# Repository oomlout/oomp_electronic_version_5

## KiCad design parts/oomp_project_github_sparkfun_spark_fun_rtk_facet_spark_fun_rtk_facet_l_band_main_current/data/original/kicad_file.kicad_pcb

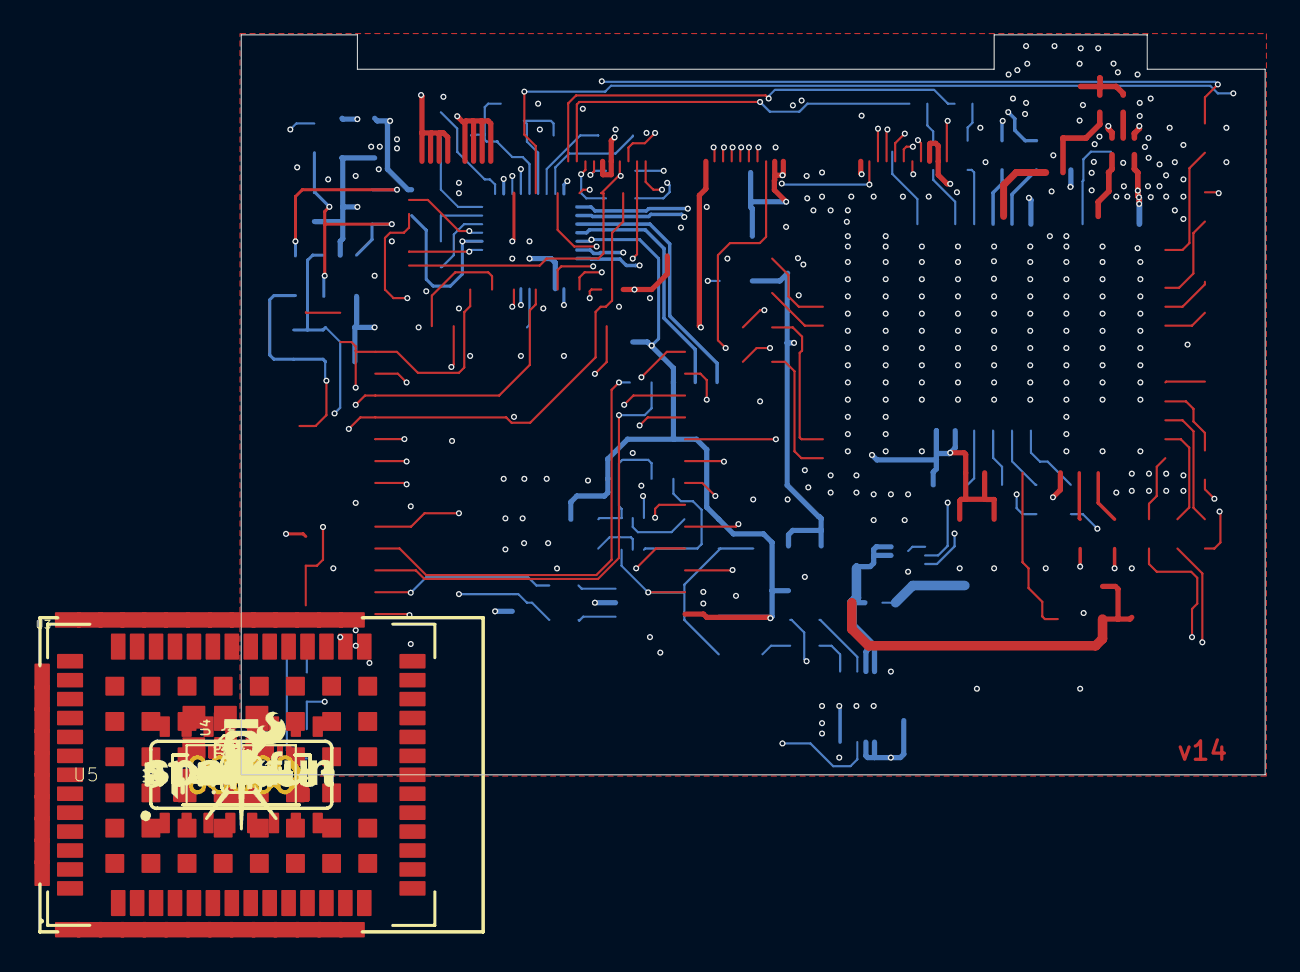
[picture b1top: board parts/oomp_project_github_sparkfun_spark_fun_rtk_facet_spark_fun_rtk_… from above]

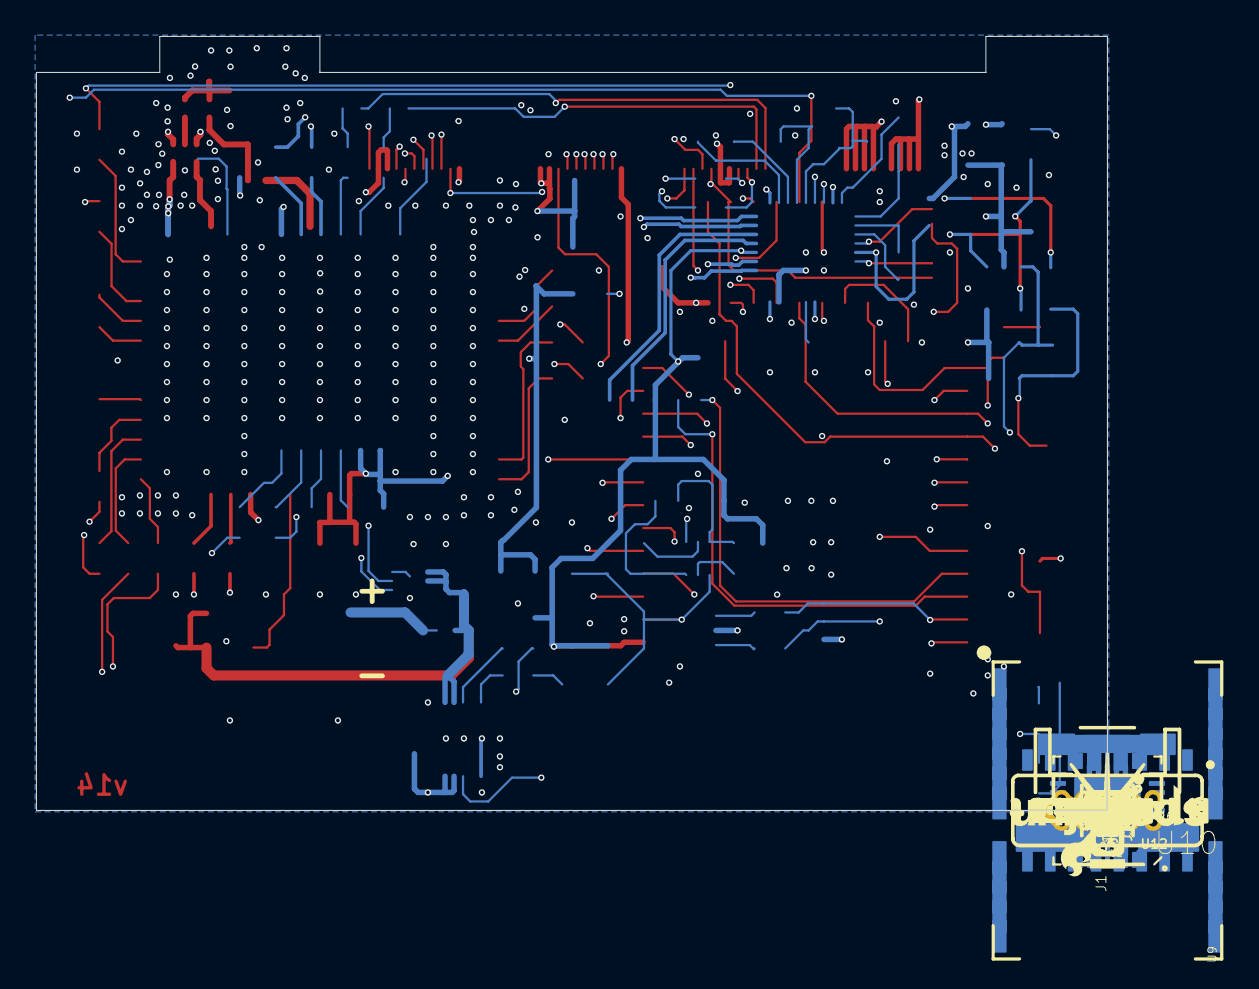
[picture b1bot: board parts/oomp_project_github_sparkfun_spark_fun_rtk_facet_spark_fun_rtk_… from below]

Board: 4 copper layers, 59.5 x 43.0 mm, 153 parts (89 on the bottom side), 109 nets.

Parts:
C2, C4, C6, C17, C18, C25, C27, C30, C31: 1.0uF; 0603
C3, C16: 4.7uF; 0603
C5, C7, C8, C11, C12, C13, C15, C21, C22, C23, C24, C26, C28, C29: 0.1uF; 0603
C9, C19: 18pF; 0603
C10, C14, C20: 10uF; 0603
C32, C33: 47pF; 0402-TIGHT
D1: Yellow; LED-0603
D2, D7: 3A/10V/280mV; SOD-323
D4: 250mA/100V; SOD-323
D5: PESD0402; 0402-TIGHT
FB2: 2.66Ω; 0402-TIGHT
FRAME1, FRAME2: FRAME-LEDGER; CREATIVE_COMMONS
J1: QWIIC_RIGHT_ANGLE; JST04_1MM_RA
J2: U.FL
J3: 1X01_NO_SILK
J4, J14: 1X02_NO_SILK
J7: JST-2-SMD
J8, J10, J15, J18: FPC_12_DOUBLESIDED_BACKFLIP
J9: CORTEX_JTAG_DEBUG_PTH; 2X5-PTH-1.27MM
JP1, JP2: SMT-JUMPER_2_NO_SILK
JP3, JP4: SMT-JUMPER_2_NC_TRACE_SILK
JP7: JUMPER-SMT_3_NO_SILK; SMT-JUMPER_3_NO_SILK
JP21, JP61, JP71, JP81: FIDUCIALUFIDUCIAL; FIDUCIAL-MICRO
LOGO1: OSHW-LOGOMINI; OSHW-LOGO-MINI
LOGO2, LOGO3: SFE_LOGO_NAME_FLAME.1_INCH; SFE_LOGO_NAME_FLAME_.1
MEAS2: JUMPER-COMBO_2_NC_TRACE; COMBO-JUMPER_2_NC_TRACE
Q2: MBT3904DW1T1; SC70-6
Q3: SIL2308; SOT26
R1, R2, R3, R4, R9, R14, R15, R35, R36, R37, R38, R41, R42, R45, R46, R47, R48, R49, R50: 33; 0603
R5: 12k; 0603
R6, R11, R33: 1k; 0603
R7, R12: 2.2k; 0603
R8: 0; 0603
R10, R20, R22, R23, R29, R31: 10k; 0603
R13: 1M; 0603
R16, R17, R18, R19, R21, R26: 100k; 0603
R24: 300k; 0603
R25, R32: 22; 0603
R27, R28, R39, R40: 27; 0603
R30: 150k; 0603
R34: 4.7k; 0603
R43: 100; 0603
R44: 10; 0402-TIGHT
TP1, TP2: TEST-POINT3X5; PAD.03X.05
U1: 74HC4052D; SO16
U2, U12: AP2112K-3.3V; SOT23-5
U3: U-BLOX_ZED-F9P; ZED-F9P
U4: STLQ015-3.3V; SOT23-5
U5: ESP-WROOM-3232D-DFMP; ESP-WROOM-32D-DFM_PASTE
U6: CH340C; SO016
U7: MAX17048; DFN-8
U8: USB251XB; QFN-36
U9: U-BLOX_NEO-D9S-00B; NEO-M9N_M8T_M8U_D9S_F9P
U10: MCP73833MSOP; MSOP10
U13: POWER-DIVIDER; PD0922J5050S2HF_ANA
U$1: LIPO0
U$2: SPECIAL_INSTRUCTIONS-ORDERING; ORDERING_INSTRUCTIONS
U$3: EC21
U$4: SD#DIS0
U$5, U$7: L#BAND0
U$6: #3V3#0
U$8: EC10
U$10: #PPS#1
U$11, U$13: RTK_FACET0
U$12: RADIO0
U$14, U$84: #GND#1
U$15, U$16: RTK5#SVG0
U$17: ANTENNA1
U$18: L1#L2#L0
U$24: STAT0
U$25: #I�C#0
U$26: ##ERST##0
U$30: QWIIC_4MM
Y1: 24MHz; CRYSTAL-SMD-2.0X1.6MM

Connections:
3.3V: C2.1, C7.2, C8.1, C25.1, C26.2, C30.1, C31.1, J1.2, J4.1, J8.3, J8.4, J10.3, J10.4, J18.5, J18.6, JP7.2, U1.16, U3.33, U3.34, U3.38, U9.7, U9.22, U9.23, U12.5
CHG_LED: J8.11, U10.3
CHG_THERM1: R8.2, R10.2, R30.2
ESP32_EN: C12.1, J9.10, J14.1, Q2.3, R20.1, U5.3
ESP32_RXI: U5.34, U6.2
ESP32_TXO: U5.35, U6.3
ESP32_~DTR: Q2.1, R23.1, U6.13
ESP32_~RTS: Q2.4, R29.1, U6.14
ESP_0/BOOT/STAT_LED/MUX_B: Q2.6, R11.2, U1.9, U5.25
ESP_2/MUX_A: U1.10, U5.24
ESP_3V3: C4.1, C5.2, C10.1, C11.1, C13.1, C14.1, J9.1, R18.2, R20.2, R34.2, U2.5, U5.2, U6.4, U6.16, U8.5, U8.10, U8.15, U8.23, U8.29, U8.36
ESP_4/RADIO_PWR_ON: J10.6, U5.26
ESP_5/RADIO_CTSI: J10.8, U5.29
ESP_12/MTDI: J9.8, U5.14
ESP_13/POWER_CTRL/MTCK: D4.A, J9.4, R22.1, R24.2, U5.16
ESP_14/PERIPHERAL_POWER/MTMS: J9.2, U5.13, U12.3
ESP_15/MTDO/RADIO_~RESET: J9.6, J10.5, U5.23
ESP_16/ZED_TXO1: R3.2, U1.12, U5.27
ESP_17/ZED_RXI1: R15.2, U1.1, U5.28
ESP_18/SD_SCK: J8.7, U5.30
ESP_19/SD_CIPO: J8.8, U5.31
ESP_21/SDA: J1.3, J8.10, J18.4, JP1.1, R4.2, R7.1, R37.2, U1.2, U5.33, U7.8
ESP_22/SCL: J1.4, J8.9, J18.3, JP2.1, R9.2, R12.1, R38.2, U1.15, U5.36, U7.7
ESP_23/SD_COPI: J8.6, U5.37
ESP_25/SD_~CS: J8.5, U5.10
ESP_26/DAC2: U1.11, U5.11
ESP_27/FAST_OFF: C20.2, Q3.G1, R24.1, U5.12
ESP_32/RADIO_TXO: J10.11, U5.8
ESP_33/RADIO_RXI: J10.10, U5.9
ESP_DM: U6.6, U8.3
ESP_DP: U6.5, U8.4
ESP_I34/RADIO_INT: J10.7, U5.6
ESP_I35/DEVICE_SENSE: R33.2, R34.1, U5.7
ESP_I36/RADIO_RTSO: J10.9, U5.4
ESP_I39/ADC39: U1.4, U5.5
EXTERNAL_SERIAL1_RXI: J18.1, U1.3
EXTERNAL_SERIAL1_TXO: J18.2, U1.13
FENCE_LV: R48.1, U3.19
GND: C2.2, C3.2, C4.2, C5.1, C6.2, C7.1, C8.2, C9.1, C10.2, C11.2, C12.2, C13.2, C14.2, C15.2, C16.2, C17.2, C18.2, C19.1, C21.2, C24.2, C25.2, C26.1, C27.2, C28.2, C29.2, C30.2, C31.2, C32.2, D1.C, D5.2, J1.1, J2.1, J2.2, J3.1, J7.1, J8.1, J9.3, J9.5, J9.7, J9.9, J10.1, J10.2, J14.2, J15.10, J15.11, J15.12, J18.11, J18.12, Q3.S1, R5.2, R6.1, R10.1, R16.1, R17.1, R19.1, R30.1, R33.1, U1.6, U1.7, U1.8, U2.2, U3.1, U3.3, U3.12, U3.14, U3.32, U3.37, U3.41, U3.48, U3.55, U3.56, U3.57, U3.58, U3.59, U3.60, U3.61, U3.62, U3.63, U3.64, U3.65, U3.66, U3.67, U3.68, U3.69, U3.70, U3.71, U3.72, U3.73, U3.74, U3.75, U3.76, U3.77, U3.78, U3.79, U3.80, U3.81, U3.82, U3.83, U3.84, U3.85, U3.86, U3.87, U3.88, U3.89, U3.90, U3.91, U3.92, U3.93, U3.94, U3.95, U3.96, U3.97, U3.98, U3.99, U3.100, U3.101, U3.102, U4.2, U5.1, U5.15, U5.38, U5.GND, U5.GNDT1, U5.GNDT2, U5.GNDT3, U5.GNDT4, U5.GNDT5, U5.GNDT6, U5.GNDT7, U5.GNDT8, U6.1, U7.1, U7.4, U7.6, U7.9, U8.11, U8.EP, U9.10, U9.12, U9.13, U9.24, U10.5, U12.2, U13.1, U13.3, U13.5
LIPO_RAW: J7.2, MEAS2.1, MEAS2.3
unnamed: R8.1, U10.8
unnamed: D1.A, R11.1
unnamed: JP7.3, R7.2
unnamed: JP7.1, R12.2
unnamed: R2.1, U3.51
unnamed: C22.1, C23.2, Q3.D1, Q3.G2, R26.1
unnamed: C9.2, R13.2, U8.33, Y1.3
unnamed: C19.2, R13.1, U8.32, Y1.1
unnamed: R5.1, U8.35
unnamed: R16.2, U8.28
unnamed: R27.2, U3.40
unnamed: R28.2, U3.39
unnamed: JP3.1, R41.2
unnamed: R17.2, U8.25
unnamed: C21.1, U8.34
unnamed: R1.1, U3.49
unnamed: C24.1, U8.14
unnamed: R50.1, U3.50
unnamed: R25.2, U8.30
unnamed: R32.2, U8.31
unnamed: JP1.2, U8.22
unnamed: R14.1, U3.46
unnamed: JP2.2, U8.24
unnamed: Q2.5, R23.2
unnamed: Q2.2, R29.2
unnamed: R39.2, U9.6
unnamed: R40.2, U9.5
unnamed: R41.1, U9.3
unnamed: R42.1, U9.4
unnamed: R35.1, U9.20
unnamed: R36.1, U9.21
unnamed: R37.1, U9.18
unnamed: R38.1, U9.19
unnamed: C32.1, FB2.2, R44.2
unnamed: JP4.1, R42.2
unnamed: C33.2, U13.2
NEO_DM: R40.1, U8.6
NEO_DP: R39.1, U8.7
NEO_RF_IN: R43.2, U9.11, U13.6
NEO_~RESET: TP1.1, U9.8
NEO_~SAFEBOOT: TP2.1, U9.1
POWER_BTN: C23.1, D4.C, J8.2, R31.1
PPS: R49.1, U3.53
PROG1: R6.2, U10.6
RF_IN: C33.1, D5.1, FB2.1, J2.FEED
RTK_LV: R47.1, U3.20
RX2_LV: R46.1, U3.26
RXLV: R15.1, U3.43
SCL_LV: R9.1, U3.45
SDA_LV: R4.1, U3.44
TX2_LV: R45.1, U3.27
TXLV: R3.1, U3.42
USB_DM: J18.8, R25.1
USB_DP: J18.7, R32.1
USB_~RESET: C28.1, R18.1, U8.26
VBUS_DET: C29.1, R19.2, R21.1, U8.27
VOUT: C6.1, C20.1, C27.1, J10.12, J15.6, J15.7, J15.8, J15.9, Q3.D2, R22.2, U2.1, U2.3, U12.1
V_BATT: C3.1, C15.1, C17.1, D7.A, MEAS2.2, MEAS2.4, U4.1, U4.3, U7.2, U7.3, U10.9, U10.10
V_RAW: C16.1, C22.2, D2.C, D7.C, Q3.S2, R26.2, R31.2, U10.1, U10.2
V_USB: D2.A, J8.12, J15.1, J15.2, J15.3, J15.4, R21.2
ZED_BACKUP: C18.1, U3.36, U4.5
ZED_DM: R28.1, U8.1
ZED_DP: R27.1, U8.2
ZED_EXTINT: R2.2, U1.5
ZED_PPS_STAT: J4.2, R49.2, U1.14
ZED_RF_IN: R43.1, U3.2, U13.4
ZED_RXI2: J18.9, JP3.2, R46.2
ZED_TXO2: J18.10, JP4.2, R45.2
ZED_VCC_RF: R44.1, U3.7

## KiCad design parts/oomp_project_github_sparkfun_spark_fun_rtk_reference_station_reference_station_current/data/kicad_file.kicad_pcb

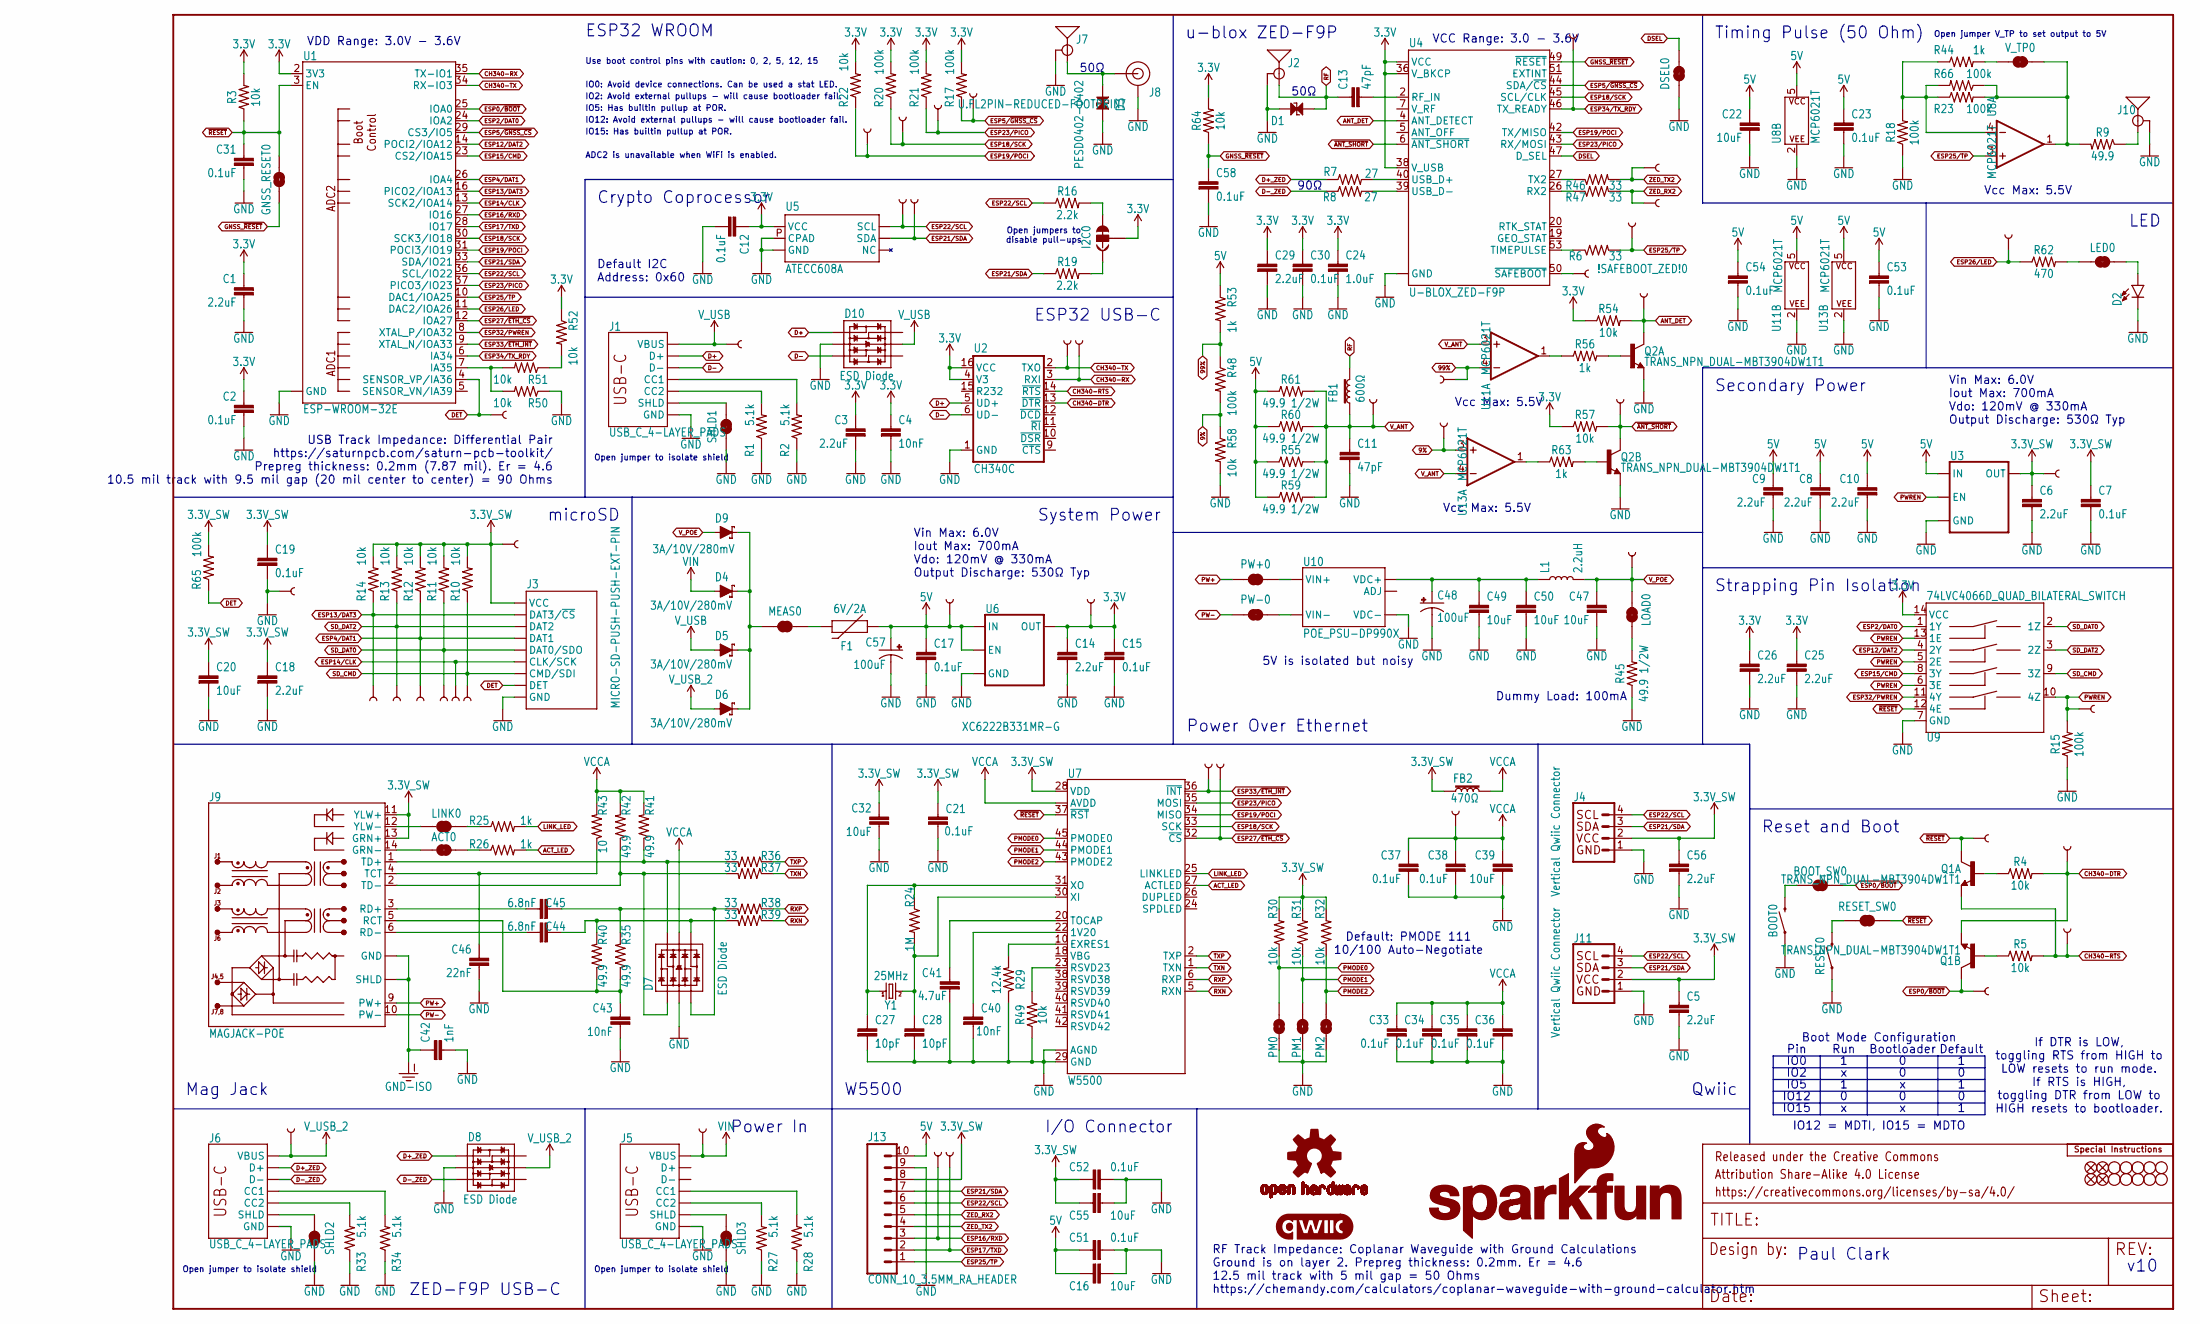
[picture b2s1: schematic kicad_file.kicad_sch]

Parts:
!SAFEBOOT_ZED!0: TEST-POINTPOGO_PTH; 1X01_NO_SILK
ACT0: JUMPER-SMT_2_NC_TRACE_SILK; SMT-JUMPER_2_NC_TRACE_SILK
ANT_DET0: TEST-POINTPOGO_PTH; 1X01_NO_SILK
ANT_SHT0: TEST-POINTPOGO_PTH; 1X01_NO_SILK
BOOT0: MOMENTARY-SWITCH-SPST-PTH-RIGHT-ANGLE-8-020; TACTILE_SWITCH_PTH_RA_8-020
BOOT_SW0: JUMPER-SMT_2_NC_TRACE_SILK; SMT-JUMPER_2_NC_TRACE_SILK
C1, C3, C5, C6, C8, C9, C10, C14, C18, C25, C26, C29, C56: 2.2uF; 0603
C2, C7, C12, C15, C17, C19, C21, C23, C30, C31, C33, C34, C35, C36, C37, C38, C51, C52, C53, C54, C58: 0.1uF; 0603
C4, C40, C43: 10nF; 0603
C11, C13: 47pF; 0603
C16, C47, C49, C50: 10uF; 0805
C20, C22, C32, C39, C55: 10uF; 0603
C24: 1.0uF; 0603
C27, C28: 10pF; 0603
C41: 4.7uF; 0603
C42: 1nF; 1206
C44, C45: 6.8nF; 0603
C46: 22nF; 0603
C48, C57: 100uF; PANASONIC_D
CLK0: TEST-POINTPOGO_PTH; 1X01_NO_SILK
CMD0, CMD1: TEST-POINTPOGO_PTH; 1X01_NO_SILK
D1, D3: PESD0402-0402; 0402; MOUSE_PART 650-PESD0402-140; DIGIKEY_PART PESD0402-140CT-ND
D2: LED-RIGHT-ANGLE-PTH-GREEN; CBI-RIGHT-ANGLE-PTH
D4, D5, D6, D9: 3A/10V/280mV; SOD-323
D7, D8, D10: ESD Diode; SOT-23-6
DAT0, DAT1, DAT2, DAT3: TEST-POINTPOGO_PTH; 1X01_NO_SILK
DET0: TEST-POINTPOGO_PTH; 1X01_NO_SILK
DSEL0: JUMPER-SMT_2_NC_TRACE_SILK; SMT-JUMPER_2_NC_TRACE_SILK
DTR0: TEST-POINTPOGO_PTH; 1X01_NO_SILK
ETH_CS0: TEST-POINTPOGO_PTH; 1X01_NO_SILK
ETH_INT0: TEST-POINTPOGO_PTH; 1X01_NO_SILK
F1: 6V/2A; 1210
FB1: 600Ω; 0805
FB2: 470Ω; 0603
FD1, FD2, FD3, FD4: FIDUCIAL1X2; FIDUCIAL-1X2
FRAME1: FRAME-LEDGER; CREATIVE_COMMONS
GND0: TEST-POINTPOGO_PTH; 1X01_NO_SILK
GNSS_CS0: TEST-POINTPOGO_PTH; 1X01_NO_SILK
GNSS_RESET0: JUMPER-COMBO_2_NO; COMBO-JUMPER_2_NO
H1, H2, H3, H4, H5, H6, H7, H8, H9, H10: STAND-OFFTIGHT; STAND-OFF-TIGHT
I2C0: JUMPER-SMT_3_2-NC_TRACE_SILK; SMT-JUMPER_3_2-NC_TRACE_SILK
J1, J5, J6: USB_C_4-LAYER_PADS; USB-C-16P_4LAYER-PADS
J2, J10: ANTENNA-SMA-GROUNDEDEDGE_SMA; SMA-EDGE
J3: MICRO-SD-PUSH-PUSH-EXT-PIN; MICROSD-EXTERNALPIN
J4, J11: Vertical Qwiic Connector; JST04_1MM_VERT
J7: ANTENNA-SMA-GROUNDEDEDGE_RPSMA; RP-SMA-EDGE
J8: U.FL2PIN-REDUCED-FOOTPRINT; U.FL_REDUCED_FOOTPRINT
J9: MAGJACK-POE; MAGJACK-SYM_LED
J13: CONN_10_3.5MM_RA_HEADER; 1X10_SCREW_TERMINAL_3.5MM
L1: 2.2uH; 0805-WIDE
LED0: JUMPER-SMT_2_NC_TRACE_SILK; SMT-JUMPER_2_NC_TRACE_SILK
LINK0: JUMPER-SMT_2_NC_TRACE_SILK; SMT-JUMPER_2_NC_TRACE_SILK
LOAD0: JUMPER-SMT_2_NC_TRACE_SILK; SMT-JUMPER_2_NC_TRACE_SILK
LOGO1: SPECIAL_INSTRUCTIONS-ORDERING; ORDERING_INSTRUCTIONS
LOGO3: QWIIC_LOGO_6MM; QWIIC_6MM
LOGO4: OSHW-LOGOS; OSHW-LOGO-S
LOGO5: SFE_LOGO_NAME.2_INCH; SFE_LOGO_NAME_.2
LOGO6: SFE_LOGO_FLAME.2_INCH; SFE_LOGO_FLAME_.2
MEAS0: JUMPER-COMBO_2_NC_TRACE; COMBO-JUMPER_2_NC_TRACE
PICO0: TEST-POINTPOGO_PTH; 1X01_NO_SILK
PM0, PM1, PM2: JUMPER-SMT_2_NO_SILK; SMT-JUMPER_2_NO_SILK
POCI0: TEST-POINTPOGO_PTH; 1X01_NO_SILK
PW+0: JUMPER-COMBO_2_NC_TRACE; COMBO-JUMPER_2_NC_TRACE
PW-0: JUMPER-COMBO_2_NC_TRACE; COMBO-JUMPER_2_NC_TRACE
PWREN0: TEST-POINTPOGO_PTH; 1X01_NO_SILK
Q1, Q2: TRANS_NPN_DUAL-MBT3904DW1T1; SC70-6
R1, R2, R27, R28, R33, R34: 5.1k; 0603
R3, R4, R5, R10, R11, R12, R13, R14, R22, R30, R31, R32, R49, R50, R51, R52, R54, R57, R58, R64: 10k; 0603
R6, R36, R37, R38, R39, R46, R47: 33; 0603
R7, R8: 27; 0603
R9, R35, R40, R41, R42: 49.9; 0603
R15, R17, R18, R20, R21, R23, R48, R65, R66: 100k; 0603
R16, R19: 2.2k; 0603
R24: 1M; 0603
R25, R26, R44, R53, R56, R63: 1k; 0603
R29: 12.4k; 0603
R43: 10; 0603
R45, R55, R59, R60, R61: 49.9 1/2W; 1206
R62: 470; 0603
RESET0: MOMENTARY-SWITCH-SPST-PTH-RIGHT-ANGLE-8-020; TACTILE_SWITCH_PTH_RA_8-020
RESET_SW0: JUMPER-SMT_2_NC_TRACE_SILK; SMT-JUMPER_2_NC_TRACE_SILK
RTS0: TEST-POINTPOGO_PTH; 1X01_NO_SILK
RX0, RX2: TEST-POINTPOGO_PTH; 1X01_NO_SILK
RXD0: TEST-POINTPOGO_PTH; 1X01_NO_SILK
SCK0: TEST-POINTPOGO_PTH; 1X01_NO_SILK
SCL0: TEST-POINTPOGO_PTH; 1X01_NO_SILK
SDA0: TEST-POINTPOGO_PTH; 1X01_NO_SILK
SHLD1, SHLD2, SHLD3: JUMPER-SMT_2_NC_TRACE_SILK; SMT-JUMPER_2_NC_TRACE_SILK
TP0: TEST-POINTPOGO_PTH; 1X01_NO_SILK
TP_BOOT0: TEST-POINTPOGO_PTH; 1X01_NO_SILK
TP_LED0: TEST-POINTPOGO_PTH; 1X01_NO_SILK
TP_RESET0: TEST-POINTPOGO_PTH; 1X01_NO_SILK
TX0, TX2: TEST-POINTPOGO_PTH; 1X01_NO_SILK
TXD0: TEST-POINTPOGO_PTH; 1X01_NO_SILK
TX_RDY0: TEST-POINTPOGO_PTH; 1X01_NO_SILK
U1: ESP-WROOM-32E; ESP-WROOM-32EU
U2: CH340C; SO016
U3, U6: XC6222B331MR-G; SOT23-5
U4: U-BLOX_ZED-F9P; ZED-F9P
U5: ATECC608A; DUAL_UDFN_2X3MM_SOIC-8
U7: W5500; LQFP-48
U8, U11, U13: MCP6021T; SOT23-5
U9: 74LVC4066D_QUAD_BILATERAL_SWITCH; SO14
U10: POE_PSU-DP990X; DP990X
UNK3V3, UNK3V3_SW0, UNK5V0, UNK9%0, UNK99%0: TEST-POINTPOGO_PTH; 1X01_NO_SILK
VANT0: TEST-POINTPOGO_PTH; 1X01_NO_SILK
VCCA0: TEST-POINTPOGO_PTH; 1X01_NO_SILK
VIN0: TEST-POINTPOGO_PTH; 1X01_NO_SILK
VPOE0: TEST-POINTPOGO_PTH; 1X01_NO_SILK
VUSB0, VUSB2: TEST-POINTPOGO_PTH; 1X01_NO_SILK
V_TP0: JUMPER-SMT_2_NC_TRACE_SILK; SMT-JUMPER_2_NC_TRACE_SILK
Y1: 25MHz; CRYSTAL-SMD-2.0X1.6MM

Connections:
3.3V: C1.1, C2.1, C3.1, C4.1, C12.1, C14.1, C15.1, C24.1, C25.1, C26.1, C29.1, C30.1, I2C0.2, R3.2, R17.2, R20.2, R21.2, R22.2, R52.1, R54.1, R57.1, R64.2, U1.2 (3V3), U2.4 (V3), U2.16 (VCC), U4.33 (VCC), U4.34 (VCC), U4.36 (V_BKCP), U4.38 (V_USB), U5.8 (VCC), U5.8S (VCC), U6.5 (OUT), U9.14 (VCC), UNK3V3.1
3.3V_SW: C5.1, C6.1, C7.1, C18.1, C19.1, C20.1, C21.1, C32.1, C52.1, C55.1, C56.1, CMD1.1, FB2.1, J3.4 (VCC), J4.2, J9.11 (YLW+), J9.13 (GRN+), J11.2, J13.8, R10.2, R11.2, R12.2, R13.2, R14.2, R30.2, R31.2, R32.2, R65.2, U3.5 (OUT), U7.28 (VDD), UNK3V3_SW0.1
5V: C8.1, C9.1, C10.1, C16.1, C17.1, C22.1, C23.1, C51.1, C53.1, C54.1, C57.+, F1.1, J13.10, R53.1, R55.1, R59.1, R60.1, R61.1, U3.1 (IN), U6.1 (IN), U6.3 (EN), U8.5 (P$V+), U11.5 (P$V+), U13.5 (P$V+), UNK5V0.1
5V_RAW: C48.+, C49.1, C50.1, L1.1, U10.1 (VDC+), U10.2 (VDC+)
9%: R48.2, R58.1, U13.3 (+IN), UNK9%0.1
99%: R48.1, R53.2, U11.4 (-IN), UNK99%0.1
ACT: ACT0.1, J9.14 (GRN-)
ACT_LED: R26.2, U7.27 (ACTLED)
ANT_DET: ANT_DET0.1, Q2.3 (C), R54.2, U4.4 (ANT_DETECT)
CH340-DTR: DTR0.1, Q1.1 (E), R4.2, U2.13 (~DTR)
CH340-RTS: Q1.4 (E), R5.2, RTS0.1, U2.14 (~RTS)
CH340-RX: TX0.1, U1.35 (TX-IO1), U2.3 (RXI)
CH340-TX: RX0.1, U1.34 (RX-IO3), U2.2 (TXO)
D+: D10.1 (IO1), J1.A6 (D+), J1.B6 (D+), U2.5 (UD+)
D+_ZED: D8.1 (IO1), J6.A6 (D+), J6.B6 (D+), R7.1
D-: D10.3 (IO2), J1.A7 (D-), J1.B7 (D-), U2.6 (UD-)
D-_ZED: D8.3 (IO2), J6.A7 (D-), J6.B7 (D-), R8.1
DET: DET0.1, J3.9 (DET), R65.1, U1.4 (SENSOR_VP/IA36)
DSEL: DSEL0.2, U4.47 (D_SEL)
ESP0/~BOOT: BOOT_SW0.1, Q1.6 (C), TP_BOOT0.1, U1.25 (IOA0)
ESP2/DAT0: U1.24 (IOA2), U9.1 (1Y)
ESP4/DAT1: DAT1.1, J3.8 (DAT1), R12.1, U1.26 (IOA4)
ESP5/~GNSS_CS: GNSS_CS0.1, R17.1, U1.29 (CS3/IO5), U4.44 (SDA/~CS)
ESP12/DAT2: U1.14 (POCI2/IOA12), U9.4 (2Y)
ESP13/DAT3: DAT3.1, J3.2 (DAT3/~CS), R14.1, U1.16 (PICO2/IOA13)
ESP14/CLK: CLK0.1, J3.5 (CLK/SCK), U1.13 (SCK2/IOA14)
ESP15/CMD: U1.23 (CS2/IOA15), U9.8 (3Y)
ESP16/RXD: J13.3, RXD0.1, U1.27 (IO16)
ESP17/TXD: J13.2, TXD0.1, U1.28 (IO17)
ESP18/SCK: R20.1, SCK0.1, U1.30 (SCK3/IO18), U4.45 (SCL/CLK), U7.33 (SCK)
ESP19/POCI: POCI0.1, R22.1, U1.31 (POCI3/IO19), U4.42 (TX/MISO), U7.34 (MISO)
ESP21/SDA: J4.3, J11.3, J13.7, R19.1, SDA0.1, U1.33 (SDA/IO21), U5.5 (SDA), U5.5S (SDA)
ESP22/SCL: J4.4, J11.4, J13.6, R16.1, SCL0.1, U1.36 (SCL/IO22), U5.6 (SCL), U5.6S (SCL)
ESP23/PICO: PICO0.1, R21.1, U1.37 (PICO3/IO23), U4.43 (RX/MOSI), U7.35 (MOSI)
ESP25/TP: J13.1, R6.2, TP0.1, U1.10 (DAC1/IOA25), U8.3 (+IN)
ESP26/LED: R62.1, TP_LED0.1, U1.11 (DAC2/IOA26)
ESP27/~ETH_CS: ETH_CS0.1, U1.12 (IOA27), U7.32 (~CS)
ESP32/PWREN: U1.8 (XTAL_P/IOA32), U9.11 (4Y)
ESP33/~ETH_INT: ETH_INT0.1, U1.9 (XTAL_N/IOA33), U7.36 (~INT)
ESP34/TX_RDY: TX_RDY0.1, U1.6 (IA34), U4.46 (TX_READY)
GND: BOOT0.1, C1.2, C2.2, C3.2, C4.2, C5.2, C6.2, C7.2, C8.2, C9.2, C10.2, C11.2, C12.2, C14.2, C15.2, C16.2, C17.2, C18.2, C19.2, C20.2, C21.2, C22.2, C23.2, C24.2, C25.2, C26.2, C27.2, C28.2, C29.2, C30.2, C31.2, C32.2, C33.2, C34.2, C35.2, C36.2, C37.2, C38.2, C39.2, C40.2, C41.2, C42.2, C43.2, C46.2, C47.2, C48.-, C49.2, C50.2, C51.2, C52.2, C53.2, C54.2, C55.2, C56.2, C57.-, C58.2, D1.2, D2.C, D3.2, D7.2 (VSS), D8.2 (VSS), D10.2 (VSS), DSEL0.1, GND0.1, J1.GND, J1.GND2 (GND), J2.GND@0 (GND), J2.GND@1 (GND), J2.GND@2 (GND), J2.GND@3 (GND), J3.6 (GND), J3.10 (GND), J3.11 (GND), J3.12 (GND), J3.13 (GND), J4.1, J5.GND, J5.GND2 (GND), J6.GND, J6.GND2 (GND), J7.GND@0 (GND), J7.GND@1 (GND), J7.GND@2 (GND), J7.GND@3 (GND), J8.1 (GND), J8.2 (GND), J10.GND@0 (GND), J10.GND@1 (GND), J10.GND@2 (GND), J10.GND@3 (GND), J11.1, J13.9, PM0.1, PM1.1, PM2.1, Q2.1 (E), Q2.4 (E), R1.1, R2.1, R15.1, R18.1, R27.1, R28.1, R29.1, R33.1, R34.1, R45.1, R49.1, R50.1, R58.2, RESET0.1, SHLD1.1, SHLD2.1, SHLD3.1, U1.1 (GND), U1.15 (GND), U1.38 (GND), U1.GND, U1.GNDT1 (GND), U1.GNDT2 (GND), U1.GNDT3 (GND), U1.GNDT4 (GND), U1.GNDT5 (GND), U1.GNDT6 (GND), U1.GNDT7 (GND), U1.GNDT8 (GND), U2.1 (GND), U3.2 (GND), U4.1 (GND), U4.3 (GND), U4.12 (GND), U4.14 (GND), U4.32 (GND), U4.37 (GND), U4.41 (GND), U4.48 (GND), U4.55 (GND), U4.56 (GND), U4.57 (GND), U4.58 (GND), U4.59 (GND), U4.60 (GND), U4.61 (GND), U4.62 (GND), U4.63 (GND), U4.64 (GND), U4.65 (GND), U4.66 (GND), U4.67 (GND), U4.68 (GND), U4.69 (GND), U4.70 (GND), U4.71 (GND), U4.72 (GND), U4.73 (GND), U4.74 (GND), U4.75 (GND), U4.76 (GND), U4.77 (GND), U4.78 (GND), U4.79 (GND), U4.80 (GND), U4.81 (GND), U4.82 (GND), U4.83 (GND), U4.84 (GND), U4.85 (GND), U4.86 (GND), U4.87 (GND), U4.88 (GND), U4.89 (GND), U4.90 (GND), U4.91 (GND), U4.92 (GND), U4.93 (GND), U4.94 (GND), U4.95 (GND), U4.96 (GND), U4.97 (GND), U4.98 (GND), U4.99 (GND), U4.100 (GND), U4.101 (GND), U4.102 (GND), U5.4 (GND), U5.4S (GND), U5.P (CPAD), U6.2 (GND), U7.3 (AGND), U7.9 (AGND), U7.14 (AGND), U7.16 (AGND), U7.19 (AGND), U7.29 (GND), U7.48 (AGND), U8.2 (P$V-), U9.7 (GND), U10.3 (VDC-), U11.2 (P$V-), U13.2 (P$V-)
GND-ISO: C42.1, J9.7 (GND), J9.8 (GND), J9.S1 (SHLD), J9.S2 (SHLD)
GNSS_~RESET: C58.1, GNSS_RESET0.1, GNSS_RESET0.3 (1), R64.1, U4.49 (~RESET)
LINK: J9.12 (YLW-), LINK0.1
LINK_LED: R25.2, U7.25 (LINKLED)
MEAS: D4.C, D5.C, D6.C, D9.C, MEAS0.2, MEAS0.4 (2)
unnamed: J1.B5 (CC2), R1.2
unnamed: J1.A5 (CC1), R2.2
unnamed: R7.2, U4.40 (USB_D+)
unnamed: Q1.2 (B), R5.1
unnamed: Q1.5 (B), R4.1
unnamed: R8.2, U4.39 (USB_D-)
unnamed: LED0.2, R62.2
unnamed: J6.SHLD1 (SHLD), J6.SHLD2 (SHLD), J6.SHLD3 (SHLD), J6.SHLD4 (SHLD), SHLD2.2
unnamed: J5.B5 (CC2), R27.2
unnamed: F1.2, MEAS0.1, MEAS0.3 (1)
unnamed: R46.1, U4.27 (TX2)
unnamed: ACT0.2, R26.1
unnamed: D3.1, J7.SIG (SIGNAL), J8.FEED (SIGNAL)
unnamed: I2C0.3, R16.2
unnamed: I2C0.1, R19.2
unnamed: J10.SIG (SIGNAL), R9.1
unnamed: R18.2, R23.1, R44.1, R66.2, U8.4 (-IN)
unnamed: C27.1, R24.1, U7.31 (XO), Y1.1
unnamed: C28.1, R24.2, U7.30 (XI), Y1.3 (2)
unnamed: LINK0.2, R25.1
unnamed: J5.A5 (CC1), R28.2
unnamed: R29.2, U7.10 (EXRES1)
unnamed: C40.1, U7.22 (1V20)
unnamed: C41.1, U7.20 (TOCAP)
unnamed: R9.2, R23.2, R66.1, U8.1 (OUT), V_TP0.2
unnamed: LOAD0.1, R45.2
unnamed: RESET0.2, RESET_SW0.2
unnamed: BOOT0.2, BOOT_SW0.2
unnamed: R49.2, U7.23 (RSVD23)
unnamed: R44.2, V_TP0.1
unnamed: R47.1, U4.26 (RX2)
unnamed: J6.B5 (CC2), R33.2
unnamed: J6.A5 (CC1), R34.2
unnamed: R56.1, U11.1 (OUT)
unnamed: R6.1, U4.53 (TIMEPULSE)
unnamed: R50.2, R51.2, U1.7 (IA35)
unnamed: Q2.5 (B), R56.2
unnamed: R51.1, R52.2
unnamed: Q2.2 (B), R63.2
unnamed: R63.1, U13.1 (OUT)
unnamed: C13.2, U4.2 (RF_IN)
unnamed: J5.SHLD1 (SHLD), J5.SHLD2 (SHLD), J5.SHLD3 (SHLD), J5.SHLD4 (SHLD), SHLD3.2
unnamed: D2.A, LED0.1
PMODE0: PM0.2, R30.1, U7.45 (PMODE0)
PMODE1: PM1.2, R31.1, U7.44 (PMODE1)
PMODE2: PM2.2, R32.1, U7.43 (PMODE2)
PW1+: PW+0.1, PW+0.3 (1), U10.5 (VIN+), U10.6 (VIN+)
PW1-: PW-0.1, PW-0.3 (1), U10.7 (VIN-), U10.8 (VIN-)
PW+: J9.9 (PW+), PW+0.2, PW+0.4 (2)
PW-: J9.10 (PW-), PW-0.2, PW-0.4 (2)
PWREN: PWREN0.1, R15.2, U3.3 (EN), U9.5 (2E), U9.6 (3E), U9.10 (4Z), U9.13 (1E)
RCT: C43.1, J9.5 (RCT), R35.1, R40.1
RD+: C45.2, J9.3 (RD+)
RD-: C44.2, J9.6 (RD-)
RF: C13.1, D1.1, FB1.2, J2.SIG (SIGNAL)
RXN: R39.1, U7.5 (RXN)
RXN1: C44.1, D7.4 (IO3), R39.2, R40.2
RXP: R38.1, U7.6 (RXP)
RXP1: C45.1, D7.3 (IO2), R35.2, R38.2
SD_CMD: CMD0.1, J3.3 (CMD/SDI), R10.1, U9.9 (3Z)
SD_DAT0: DAT0.1, J3.7 (DAT0/SDO), R11.1, U9.2 (1Z)
SD_DAT2: DAT2.1, J3.1 (DAT2), R13.1, U9.3 (2Z)
SHIELD: J1.SHLD1 (SHLD), J1.SHLD2 (SHLD), J1.SHLD3 (SHLD), J1.SHLD4 (SHLD), SHLD1.2
TCT: C46.1, J9.4 (TCT), R43.1
TD+: D7.6 (IO4), J9.1 (TD+), R36.2, R41.1
TD-: D7.1 (IO1), J9.2 (TD-), R37.2, R42.1
TXN: R37.1, U7.1 (TXN)
TXP: R36.1, U7.2 (TXP)
VCCA: C33.1, C34.1, C35.1, C36.1, C37.1, C38.1, C39.1, D7.5 (VCC), FB2.2, R41.2, R42.2, R43.2, U7.4 (AVDD), U7.8 (AVDD), U7.11 (AVDD), U7.15 (AVDD), U7.17 (AVDD), U7.21 (AVDD), VCCA0.1
VIN: D4.A, J5.VBUS1 (VBUS), J5.VBUS2 (VBUS), VIN0.1
V_ANT: C11.1, FB1.1, R55.2, R59.2, R60.2, R61.2, U11.3 (+IN), U13.4 (-IN), VANT0.1
V_POE: C47.1, D9.A, L1.2, LOAD0.2, VPOE0.1
V_USB: D5.A, D10.5 (VCC), J1.VBUS1 (VBUS), J1.VBUS2 (VBUS), VUSB0.1
V_USB_2: D6.A, D8.5 (VCC), J6.VBUS1 (VBUS), J6.VBUS2 (VBUS), VUSB2.1
ZED_RX2: J13.5, R47.2, RX2.1
ZED_TX2: J13.4, R46.2, TX2.1
~ANT_SHORT: ANT_SHT0.1, Q2.6 (C), R57.2, U4.6 (~ANT_SHORT)
~RESET: C31.1, GNSS_RESET0.2, GNSS_RESET0.4 (2), Q1.3 (C), R3.1, RESET_SW0.1, TP_RESET0.1, U1.3 (EN), U7.37 (~RST), U9.12 (4E)
~SAFEBOOT_ZED: !SAFEBOOT_ZED!0.1, U4.50 (~SAFEBOOT)

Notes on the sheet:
VDD Range: 3.0V - 3.6V
Dummy Load: 100mA
Vcc Max: 5.5V
If DTR is LOW, toggling RTS from HIGH to LOW resets to run mode. If RTS is HIGH, toggling DTR from LOW to HIGH resets to bootloader.
50Ω
RF Track Impedance: Coplanar Waveguide with Ground Calculations Ground is on layer 2. Prepreg thickness: 0.2mm. Er = 4.6 12.5 mil track with 5 mil gap = 50 Ohms https://chemandy.com/calculators/coplanar-waveguide-with-ground-calculator.htm
VCC Range: 3.0 - 3.6V
Open jumper to isolate shield
IO2
v10
Open jumper V_TP to set output to 5V
Run
ESP32 WROOM
ZED-F9P USB-C
Power In
Reset and Boot
LED
IO15
Paul Clark
IO0: Avoid device connections. Can be used a stat LED.
IO12 = MDTI, IO15 = MDTO
IO5
Pin
IO0
Strapping Pin Isolation
System Power
5V is isolated but noisy
IO5: Has builtin pullup at POR.
I/O Connector
Power Over Ethernet
Vin Max: 6.0V Iout Max: 700mA Vdo: 120mV @ 330mA Output Discharge: 530Ω Typ
Default I2C Address: 0x60
IO2: Avoid external pullups - will cause bootloader fail.
Secondary Power
IO15: Has builtin pullup at POR.
USB Track Impedance: Differential Pair https://saturnpcb.com/saturn-pcb-toolkit/ Prepreg thickness: 0.2mm (7.87 mil). Er = 4.6 10.5 mil track with 9.5 mil gap (20 mil center to center) = 90 Ohms
Default: PMODE 111 10/100 Auto-Negotiate
microSD
Bootloader
Crypto Coprocessor

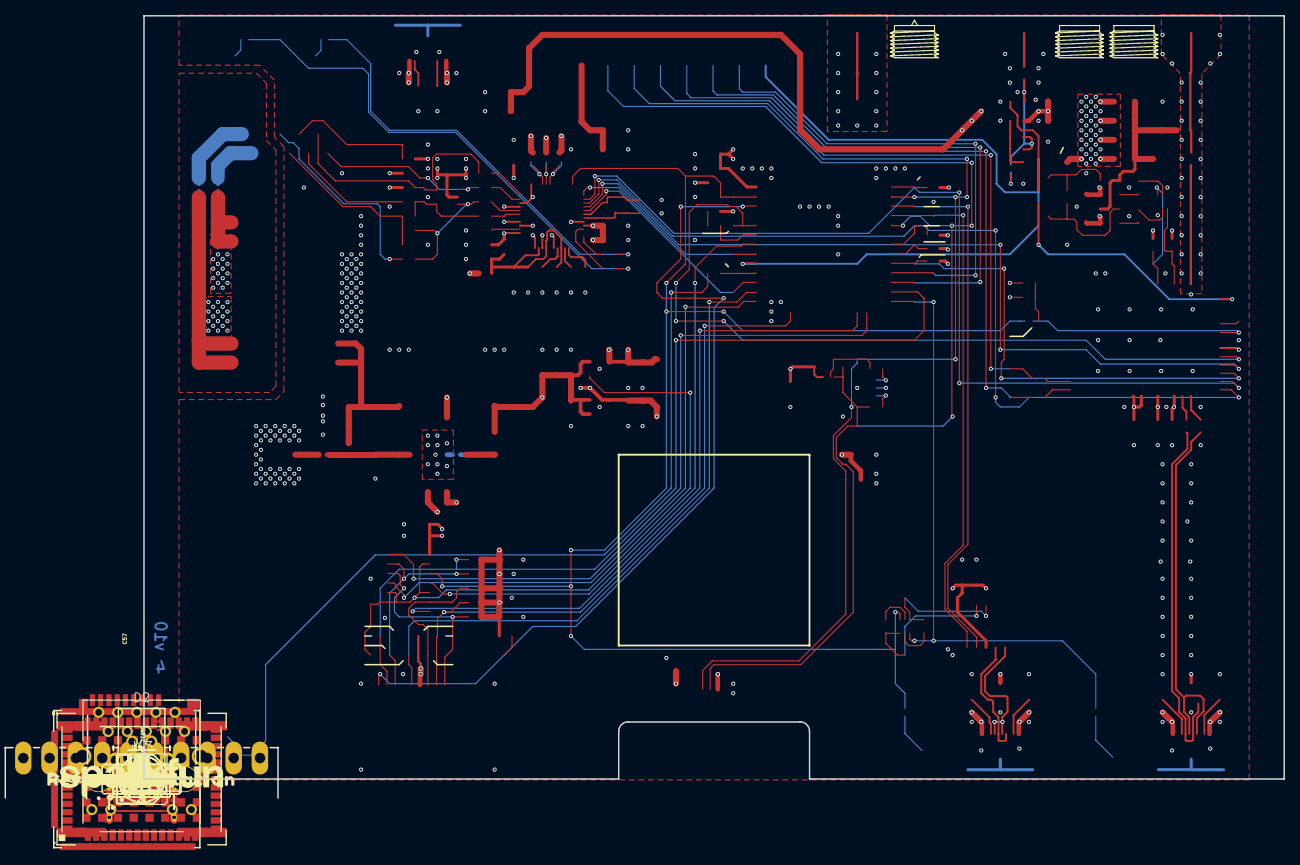
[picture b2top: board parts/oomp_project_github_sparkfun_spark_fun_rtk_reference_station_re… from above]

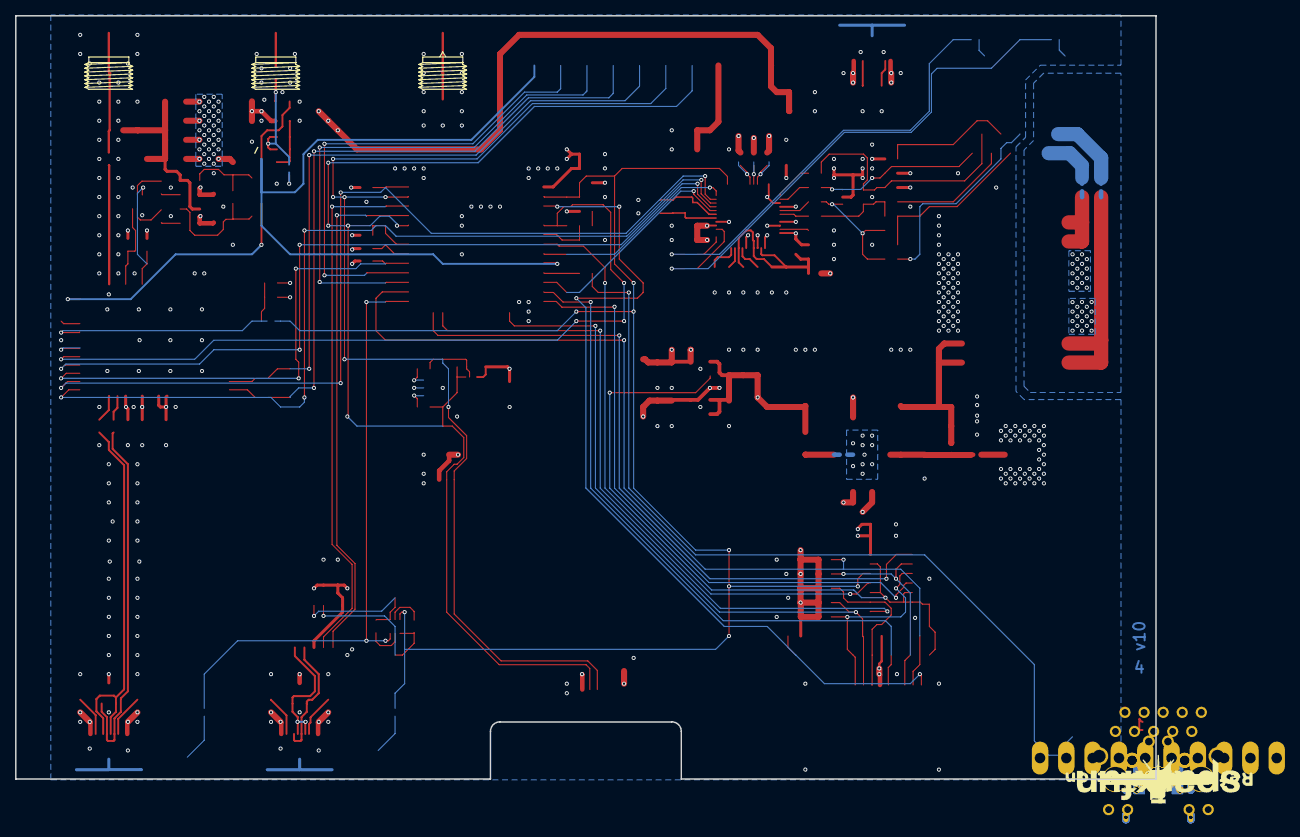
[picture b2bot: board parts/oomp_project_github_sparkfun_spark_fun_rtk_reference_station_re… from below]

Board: 4 copper layers, 151.8 x 101.6 mm, 404 parts (98 on the bottom side), 125 nets.

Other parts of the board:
LOGO2: QWIIC_LOGO_6MM; QWIIC_6MM
LOGO7: SFE_LOGO_NAME.2_INCH; SFE_LOGO_NAME_.2
LOGO8: SFE_LOGO_FLAME.2_INCH; SFE_LOGO_FLAME_.2
U$2, U$148: RESET0
U$3, U$4, U$45: #SHLD#0
U$5, U$113: PW#0
U$6, U$114: PW#1
U$7, U$37, U$96, U$149: 0_#_BOOT0
U$8: POWER_IN0
U$9: #ACT#0
U$10: #LINK#1
U$11, U$115: #3V3_SW#0
U$12, U$124: #5V#0
U$13, U$123: #GND#6
U$14: #ZED_RX2#0
U$15, U$117: #SCL#8
U$16, U$116: #SDA#7
U$17: #ZED_RX2#3
U$18: #ZED_TX2#0
U$19: #ZED_TX2#3
U$20: #16_#_RXD#0
U$21: ESP32_WIFI_#_BT0
U$22: TP0
U$23: ZED_RF0
U$24, U$107: VCCA0
U$25, U$74, U$112: #RESET#0
U$26, U$108: 34_#_TX_RDY0
U$27, U$109: 33_#_#ETH_INT#0
U$28, U$110: 26_#_LED0
U$29, U$111: 27_#_#ETH_CS#0
U$30, U$98: 23_#_PICO23
U$31, U$89: 22_#_SCL20
U$32, U$102: 18_#_SCK6
U$33, U$101: 19_#_POCI19
U$34, U$99: 1_#_TX20
U$35, U$100: 3_#_RX20
U$36, U$97: 5_#_#GNSS_CS#1
U$38, U$90: 21_#_SDA24
U$39, U$91: ZED_RX224
U$40, U$92: ZED_TX2225
U$41, U$93: #SAFEBOOT#2226
U$42, U$94: ANT_DET2227
U$43, U$95: #ANT_SHT#2228
U$44, U$106: 9#2230
U$46: #I�C#0
U$47, U$104: 99#2230
U$48, U$103: TP2230
U$49, U$105: V_ANT2229
U$55, U$76: RTS2231
U$56, U$77: DTR2232
U$57, U$144: 3V3_SW15
U$58: #LED#2234
U$59, U$88: 3V3_SW25
U$60, U$87: 3V325
U$61, U$86: 5V25
U$62, U$84: MEAS2
U$63, U$85: VIN1
U$64, U$82: V_USB3
U$65, U$83: V_USB24
U$66, U$81: V_POE0
U$67: #PMODE0#0
U$68: #PMODE1#1
U$69: #PMODE2#2
U$70: #GNSS_#RESET##0
U$71: #V_TP#3
U$72: #DSEL#0
U$73, U$75: REFERENCE_STATION1
U$78: ESP320
U$79: ZED#F9P321
U$80, U$141: PWR_EN2233
U$118: #16_#_RXD#17
U$119: #17_#_TXD#0
U$120: #17_#_TXD#18
U$121: #TP#0
U$122: #TP#1
U$125, U$126: 16_#_RXD18
U$127, U$128: 17_#_TXD0
U$129, U$139: CLK13
U$130, U$138: CMD14
U$131, U$142: DAT10
U$132, U$140: DAT011
U$133, U$145: DAT315
U$134, U$137: DAT2316
U$135, U$143: GND12
U$136: POE_LOAD0
U$146, U$147: HIGH_TEMP_WARNING
U$150, U$151: 250
U$152, U$153: RTK5#SVG0
U$154: #GNSS_RESET#0
U$155, U$156: DET0

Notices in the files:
parts/oomp_project_github_sparkfun_spark_fun_rtk_facet_spark_fun_rtk_facet_main_current/data/kicad_file.kicad_sch:
Released under the Creative Commons
https://creativecommons.org/licenses/by-sa/4.0
parts and their libraries:
Released under the Creative Commons Attribution Share-Alike 4.0 License
